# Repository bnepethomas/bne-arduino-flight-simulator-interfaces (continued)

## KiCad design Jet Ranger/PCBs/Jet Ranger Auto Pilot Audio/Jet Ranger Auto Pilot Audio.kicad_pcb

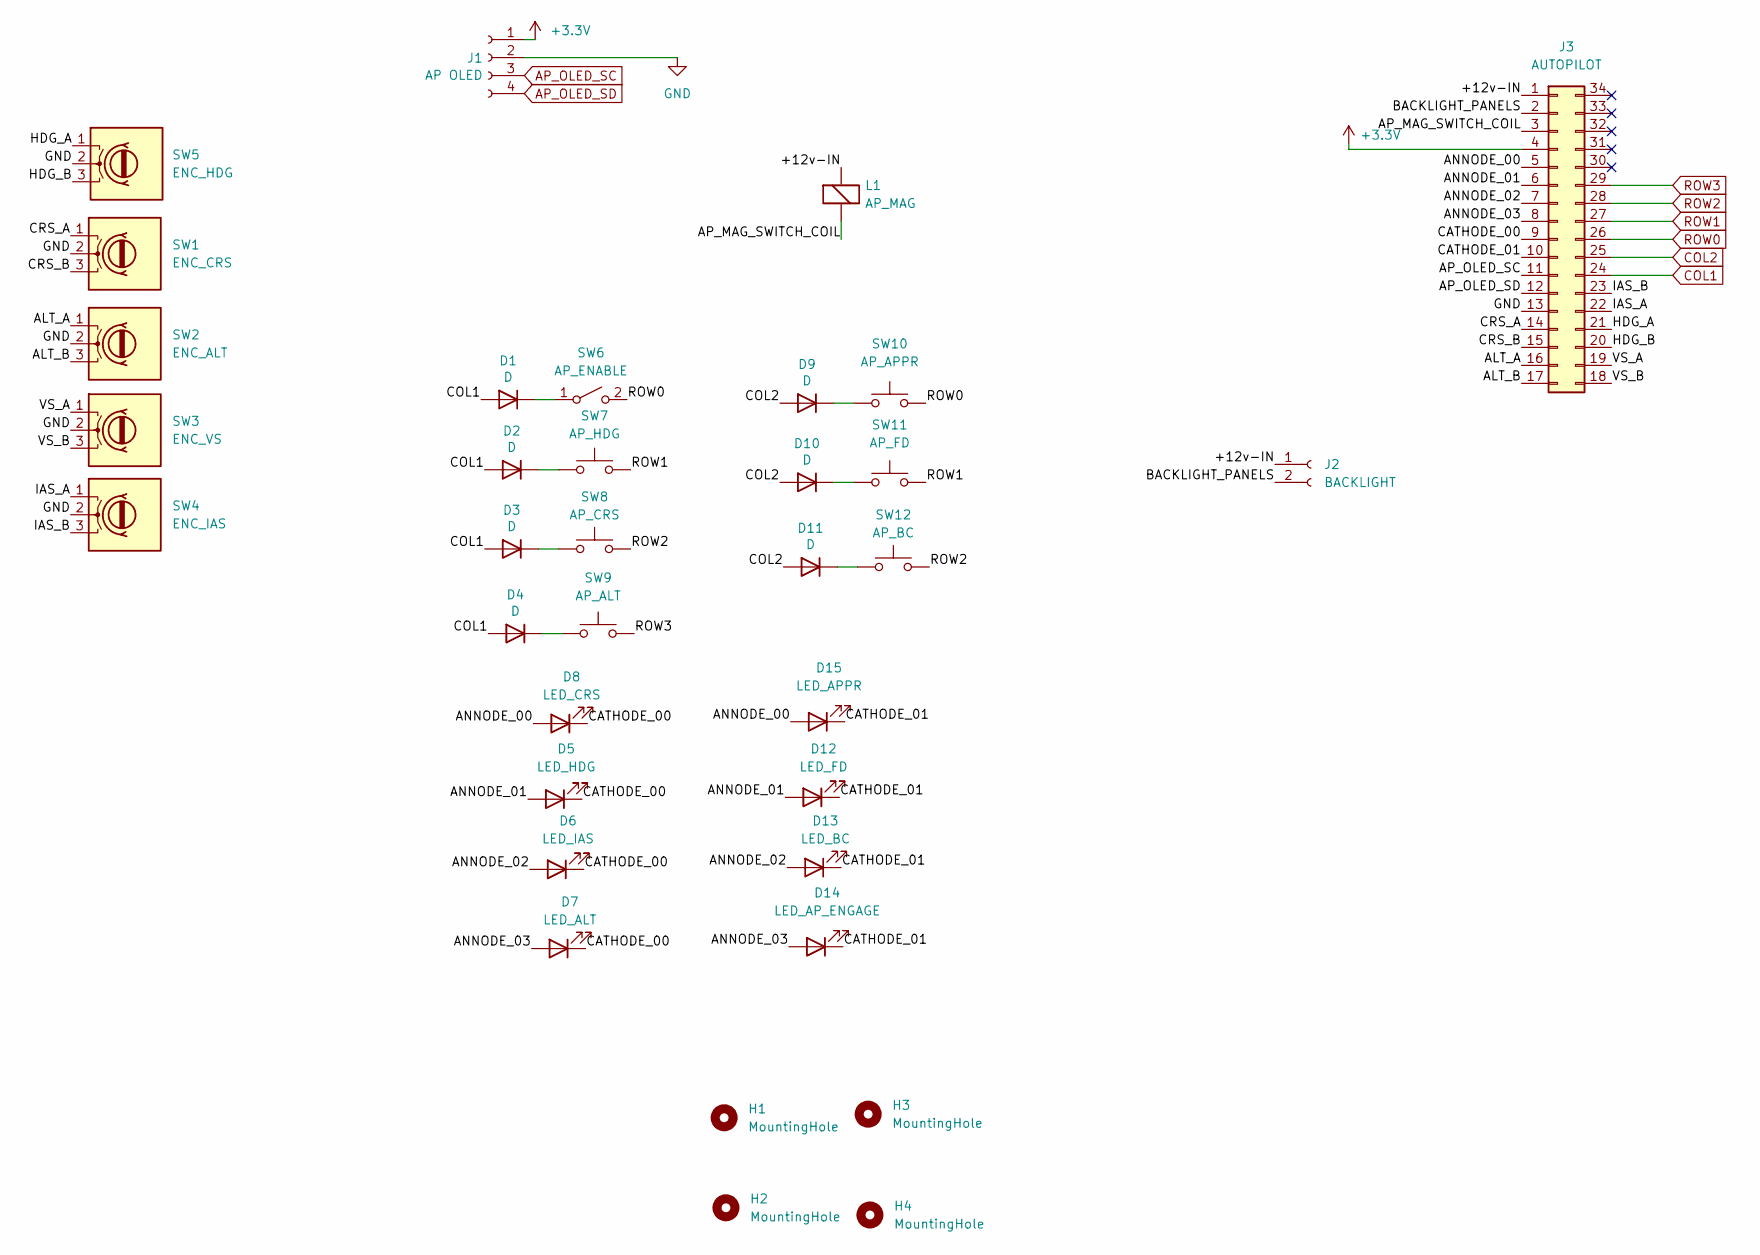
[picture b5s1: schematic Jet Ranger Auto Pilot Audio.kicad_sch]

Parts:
D1, D2, D3, D4, D9, D10, D11: D; D_A-405_P7.62mm_Horizontal
D5: LED_HDG; JST_XH_B2B-XH-A_1x02_P2.50mm_Vertical
D6: LED_IAS; JST_XH_B2B-XH-A_1x02_P2.50mm_Vertical
D7: LED_ALT; JST_XH_B2B-XH-A_1x02_P2.50mm_Vertical
D8: LED_CRS; JST_XH_B2B-XH-A_1x02_P2.50mm_Vertical
D12: LED_FD; JST_XH_B2B-XH-A_1x02_P2.50mm_Vertical
D13: LED_BC; JST_XH_B2B-XH-A_1x02_P2.50mm_Vertical
D14: LED_AP_ENGAGE; JST_XH_B2B-XH-A_1x02_P2.50mm_Vertical
D15: LED_APPR; JST_XH_B2B-XH-A_1x02_P2.50mm_Vertical
H1, H2, H3, H4: MountingHole; MountingHole_3.2mm_M3
J1: AP OLED; JST_XH_B4B-XH-A_1x04_P2.50mm_Vertical
J2: BACKLIGHT; JST_XH_B2B-XH-A_1x02_P2.50mm_Vertical
J3: AUTOPILOT; IDC-Header_2x17_P2.54mm_Vertical
L1: AP_MAG; JST_XH_B2B-XH-A_1x02_P2.50mm_Vertical
SW1: ENC_CRS; JST_XH_B3B-XH-A_1x03_P2.50mm_Vertical
SW2: ENC_ALT; JST_XH_B3B-XH-A_1x03_P2.50mm_Vertical
SW3: ENC_VS; JST_XH_B3B-XH-A_1x03_P2.50mm_Vertical
SW4: ENC_IAS; JST_XH_B3B-XH-A_1x03_P2.50mm_Vertical
SW5: ENC_HDG; JST_XH_B3B-XH-A_1x03_P2.50mm_Vertical
SW6: AP_ENABLE; JST_XH_B2B-XH-A_1x02_P2.50mm_Vertical
SW7: AP_HDG; JST_XH_B2B-XH-A_1x02_P2.50mm_Vertical
SW8: AP_CRS; JST_XH_B2B-XH-A_1x02_P2.50mm_Vertical
SW9: AP_ALT; JST_XH_B2B-XH-A_1x02_P2.50mm_Vertical
SW10: AP_APPR; JST_XH_B2B-XH-A_1x02_P2.50mm_Vertical
SW11: AP_FD; JST_XH_B2B-XH-A_1x02_P2.50mm_Vertical
SW12: AP_BC; JST_XH_B2B-XH-A_1x02_P2.50mm_Vertical

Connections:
+3.3V: J1.1, J3.4
/+12v-IN: J2.1, J3.1, L1.1 (-)
/ALT_A: J3.16, SW2.1 (A)
/ALT_B: J3.17, SW2.3 (B)
/ANNODE_00: D8.1 (A), D15.1 (A), J3.5
/ANNODE_01: D5.1 (A), D12.1 (A), J3.6
/ANNODE_02: D6.1 (A), D13.1 (A), J3.7
/ANNODE_03: D7.1 (A), D14.1 (A), J3.8
/AP_MAG_SWITCH_COIL: J3.3, L1.2 (+)
/BACKLIGHT_PANELS: J2.2, J3.2
/CATHODE_00: D5.2 (K), D6.2 (K), D7.2 (K), D8.2 (K), J3.9
/CATHODE_01: D12.2 (K), D13.2 (K), D14.2 (K), D15.2 (K), J3.10
/CRS_A: J3.14, SW1.1 (A)
/CRS_B: J3.15, SW1.3 (B)
/HDG_A: J3.21, SW5.1 (A)
/HDG_B: J3.20, SW5.3 (B)
/IAS_A: J3.22, SW4.1 (A)
/IAS_B: J3.23, SW4.3 (B)
/VS_A: J3.19, SW3.1 (A)
/VS_B: J3.18, SW3.3 (B)
AP_OLED_SC: J1.3, J3.11
AP_OLED_SD: J1.4, J3.12
COL1: D1.2 (A), D2.2 (A), D3.2 (A), D4.2 (A), J3.24
COL2: D9.2 (A), D10.2 (A), D11.2 (A), J3.25
GND: J1.2, J3.13, SW1.2 (C), SW2.2 (C), SW3.2 (C), SW4.2 (C), SW5.2 (C)
unnamed: D1.1 (K), SW6.1 (A)
unnamed: D2.1 (K), SW7.1
unnamed: D3.1 (K), SW8.1
unnamed: D4.1 (K), SW9.1
unnamed: D9.1 (K), SW10.1
unnamed: D10.1 (K), SW11.1
unnamed: D11.1 (K), SW12.1
ROW0: J3.26, SW6.2 (B), SW10.2
ROW1: J3.27, SW7.2, SW11.2
ROW2: J3.28, SW8.2, SW12.2
ROW3: J3.29, SW9.2

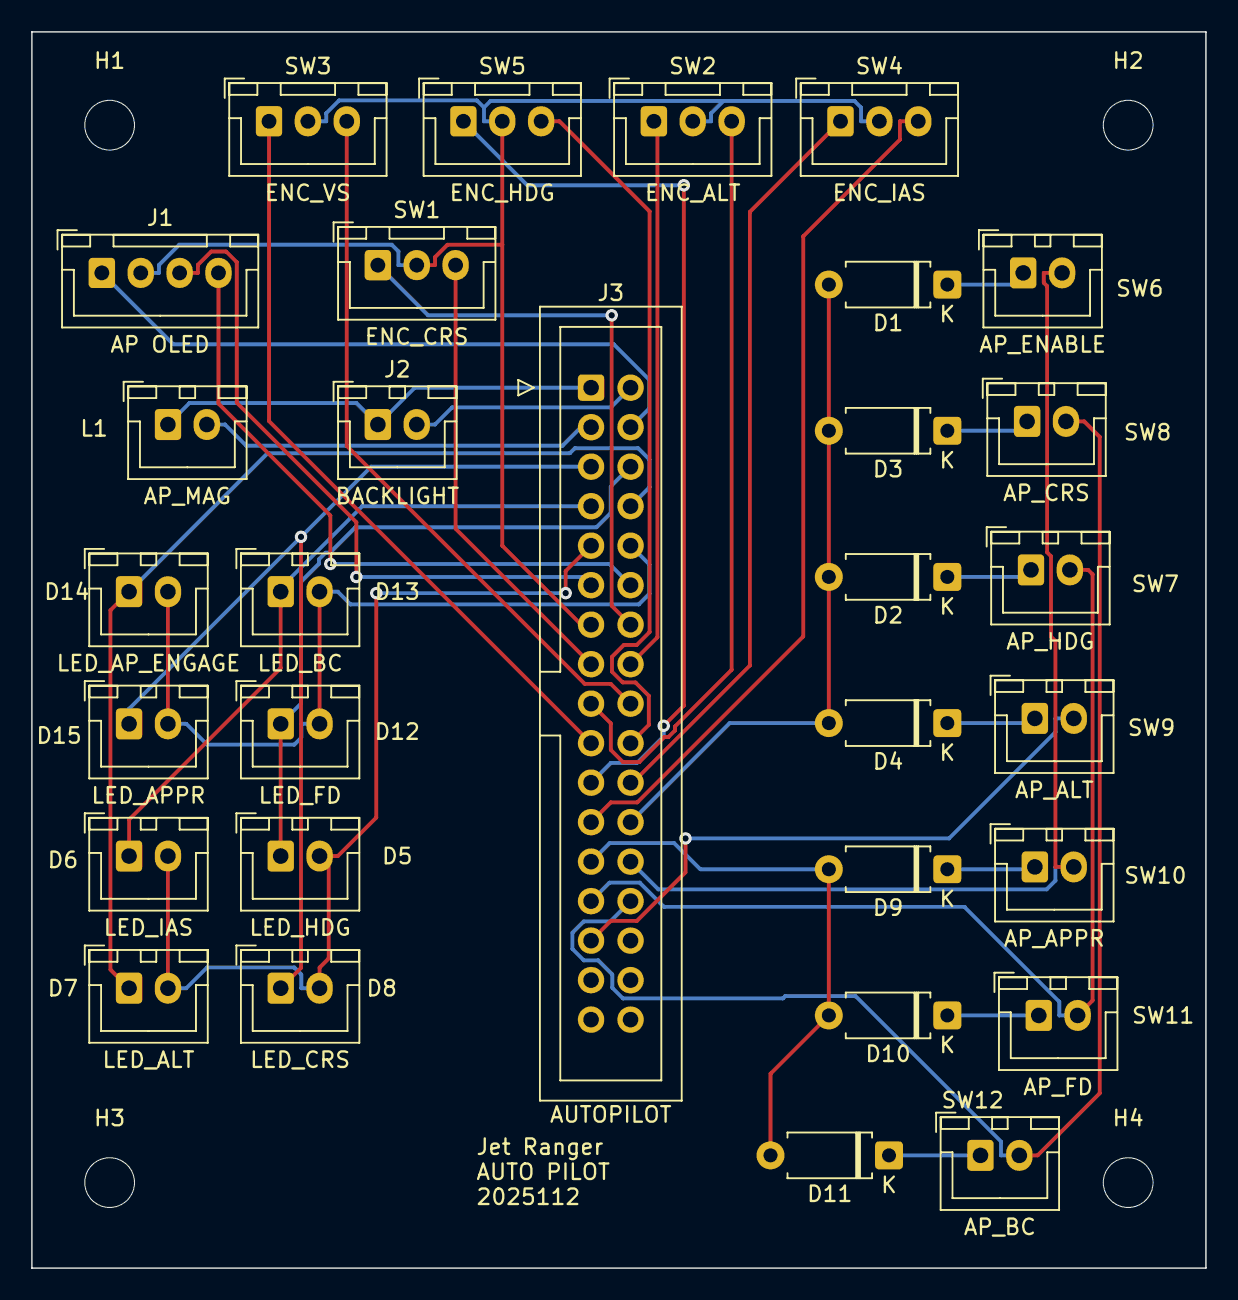
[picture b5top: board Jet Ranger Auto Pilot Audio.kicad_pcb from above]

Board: 2 copper layers, 75.5 x 79.5 mm, 35 parts (0 on the bottom side), 36 nets.
